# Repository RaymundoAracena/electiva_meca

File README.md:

# electiva_meca
aqui subire todas las tareas de electiva mecatronica

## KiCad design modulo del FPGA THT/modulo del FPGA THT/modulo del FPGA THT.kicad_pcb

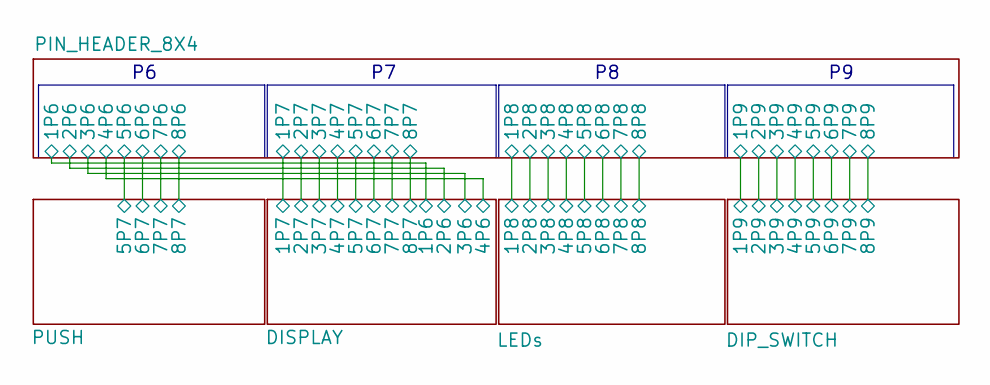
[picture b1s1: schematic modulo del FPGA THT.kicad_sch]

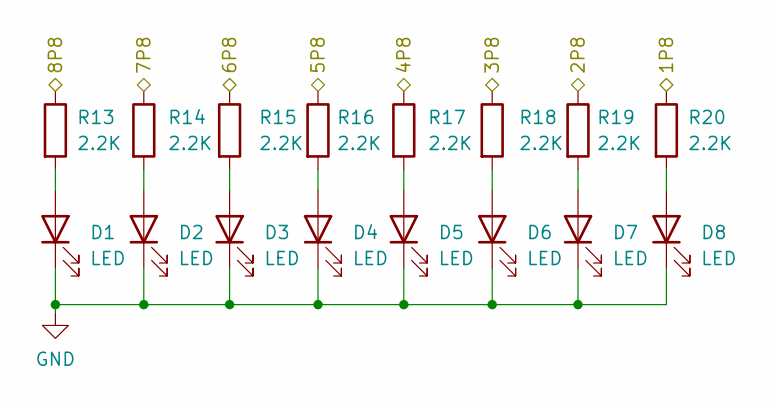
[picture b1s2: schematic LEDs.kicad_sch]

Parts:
D1, D2, D3, D4, D5, D6, D7, D8: LED; LED_0805_2012Metric
R13, R14, R15, R16, R17, R18, R19, R20: 2.2K; R_0805_2012Metric

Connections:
/LEDs/1P8: R20.1; also elsewhere on the board
/LEDs/2P8: R19.1; also elsewhere on the board
/LEDs/3P8: R18.1; also elsewhere on the board
/LEDs/4P8: R17.1; also elsewhere on the board
/LEDs/5P8: R16.1; also elsewhere on the board
/LEDs/6P8: R15.1; also elsewhere on the board
/LEDs/7P8: R14.1; also elsewhere on the board
/LEDs/8P8: R13.1; also elsewhere on the board
GND: D1.1 (K), D2.1 (K), D3.1 (K), D4.1 (K), D5.1 (K), D6.1 (K), D7.1 (K), D8.1 (K); also elsewhere on the board
unnamed: D1.2 (A), R13.2
unnamed: D2.2 (A), R14.2
unnamed: D3.2 (A), R15.2
unnamed: D4.2 (A), R16.2
unnamed: D5.2 (A), R17.2
unnamed: D6.2 (A), R18.2
unnamed: D7.2 (A), R19.2
unnamed: D8.2 (A), R20.2

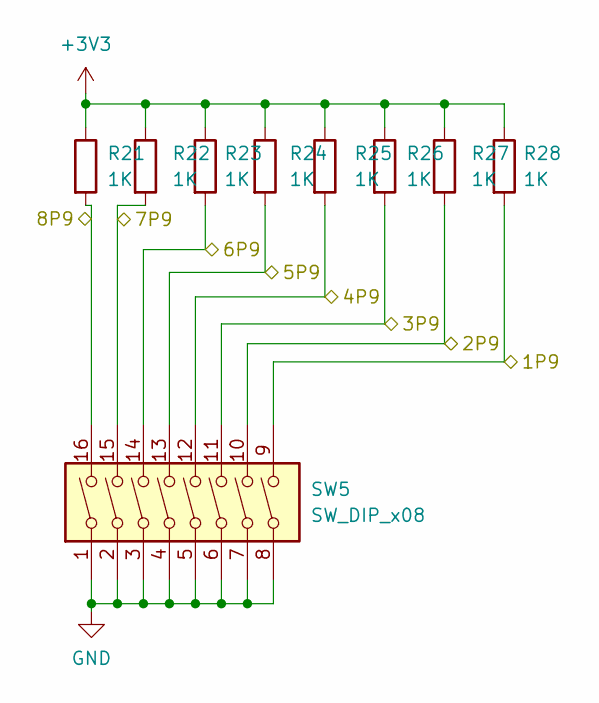
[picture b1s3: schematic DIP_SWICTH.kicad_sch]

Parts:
R21, R22, R23, R24, R25, R26, R27, R28: 1K; R_0805_2012Metric
SW5: SW_DIP_x08; SW_DIP_SPSTx08_Slide_6.7x21.88mm_W7.62mm_P2.54mm_LowProfile

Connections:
+3V3: R21.1, R22.1, R23.1, R24.1, R25.1, R26.1, R27.1, R28.1; also elsewhere on the board
/DIP_SWITCH/1P9: R28.2, SW5.9; also elsewhere on the board
/DIP_SWITCH/2P9: R27.2, SW5.10; also elsewhere on the board
/DIP_SWITCH/3P9: R26.2, SW5.11; also elsewhere on the board
/DIP_SWITCH/4P9: R25.2, SW5.12; also elsewhere on the board
/DIP_SWITCH/5P9: R24.2, SW5.13; also elsewhere on the board
/DIP_SWITCH/6P9: R23.2, SW5.14; also elsewhere on the board
/DIP_SWITCH/7P9: R22.2, SW5.15; also elsewhere on the board
/DIP_SWITCH/8P9: R21.2, SW5.16; also elsewhere on the board
GND: SW5.1, SW5.2, SW5.3, SW5.4, SW5.5, SW5.6, SW5.7, SW5.8; also elsewhere on the board

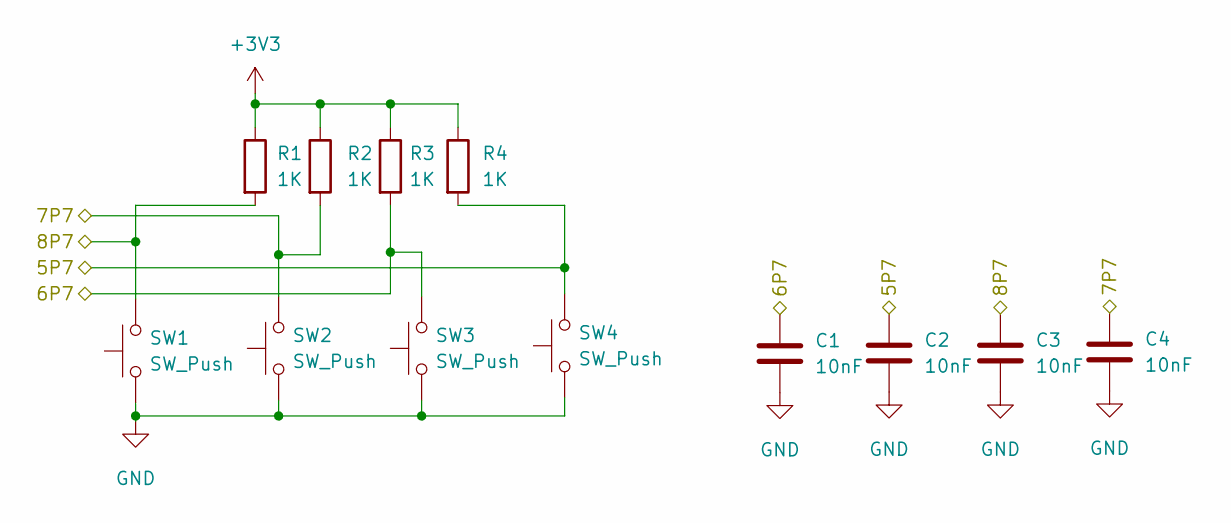
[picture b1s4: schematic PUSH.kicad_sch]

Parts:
C1, C2, C3, C4: 10nF; C_0805_2012Metric
R1, R2, R3, R4: 1K; R_0805_2012Metric
SW1, SW2, SW3, SW4: SW_Push; SW_PUSH_6mm

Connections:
+3V3: R1.1, R2.1, R3.1, R4.1; also elsewhere on the board
/PIN_HEADER_8X4/5P6: C2.1, R4.2, SW4.2; also elsewhere on the board
/PIN_HEADER_8X4/6P6: C1.1, R3.2, SW3.2; also elsewhere on the board
/PIN_HEADER_8X4/7P6: C4.1, R2.2, SW2.2; also elsewhere on the board
/PIN_HEADER_8X4/8P6: C3.1, R1.2, SW1.2; also elsewhere on the board
GND: C1.2, C2.2, C3.2, C4.2, SW1.1, SW2.1, SW3.1, SW4.1; also elsewhere on the board

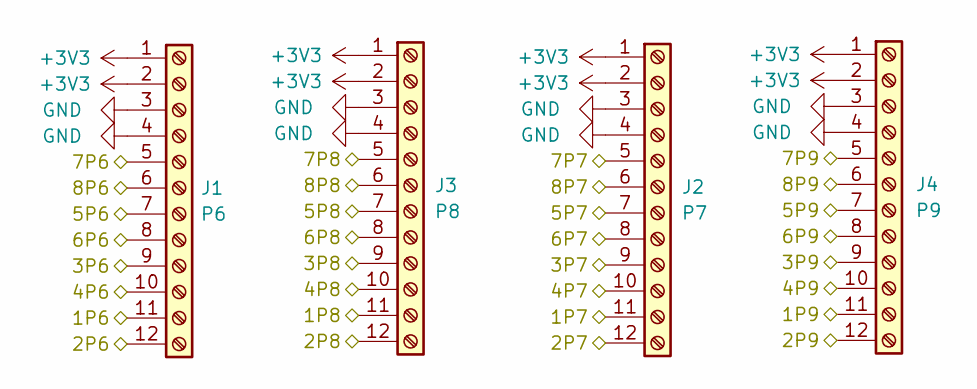
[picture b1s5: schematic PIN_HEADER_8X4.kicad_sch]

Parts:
J1: P6; PinHeader_2x06_P2.54mm_Horizontal
J2: P7; PinHeader_2x06_P2.54mm_Horizontal
J3: P8; PinHeader_2x06_P2.54mm_Horizontal
J4: P9; PinHeader_2x06_P2.54mm_Horizontal

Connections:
+3V3: J1.1, J1.2, J2.1, J2.2, J3.1, J3.2, J4.1, J4.2; also elsewhere on the board
/DIP_SWITCH/1P9: J4.11; also elsewhere on the board
/DIP_SWITCH/2P9: J4.12; also elsewhere on the board
/DIP_SWITCH/3P9: J4.9; also elsewhere on the board
/DIP_SWITCH/4P9: J4.10; also elsewhere on the board
/DIP_SWITCH/5P9: J4.7; also elsewhere on the board
/DIP_SWITCH/6P9: J4.8; also elsewhere on the board
/DIP_SWITCH/7P9: J4.5; also elsewhere on the board
/DIP_SWITCH/8P9: J4.6; also elsewhere on the board
/DISPLAY/1P6: J1.11; also elsewhere on the board
/DISPLAY/1P7: J2.11; also elsewhere on the board
/DISPLAY/2P6: J1.12; also elsewhere on the board
/DISPLAY/2P7: J2.12; also elsewhere on the board
/DISPLAY/3P6: J1.9; also elsewhere on the board
/DISPLAY/3P7: J2.9; also elsewhere on the board
/DISPLAY/4P6: J1.10; also elsewhere on the board
/DISPLAY/4P7: J2.10; also elsewhere on the board
/DISPLAY/5P7: J2.7; also elsewhere on the board
/DISPLAY/6P7: J2.8; also elsewhere on the board
/DISPLAY/7P7: J2.5; also elsewhere on the board
/DISPLAY/8P7: J2.6; also elsewhere on the board
/LEDs/1P8: J3.11; also elsewhere on the board
/LEDs/2P8: J3.12; also elsewhere on the board
/LEDs/3P8: J3.9; also elsewhere on the board
/LEDs/4P8: J3.10; also elsewhere on the board
/LEDs/5P8: J3.7; also elsewhere on the board
/LEDs/6P8: J3.8; also elsewhere on the board
/LEDs/7P8: J3.5; also elsewhere on the board
/LEDs/8P8: J3.6; also elsewhere on the board
/PIN_HEADER_8X4/5P6: J1.7; also elsewhere on the board
/PIN_HEADER_8X4/6P6: J1.8; also elsewhere on the board
/PIN_HEADER_8X4/7P6: J1.5; also elsewhere on the board
/PIN_HEADER_8X4/8P6: J1.6; also elsewhere on the board
GND: J1.3, J1.4, J2.3, J2.4, J3.3, J3.4, J4.3, J4.4; also elsewhere on the board

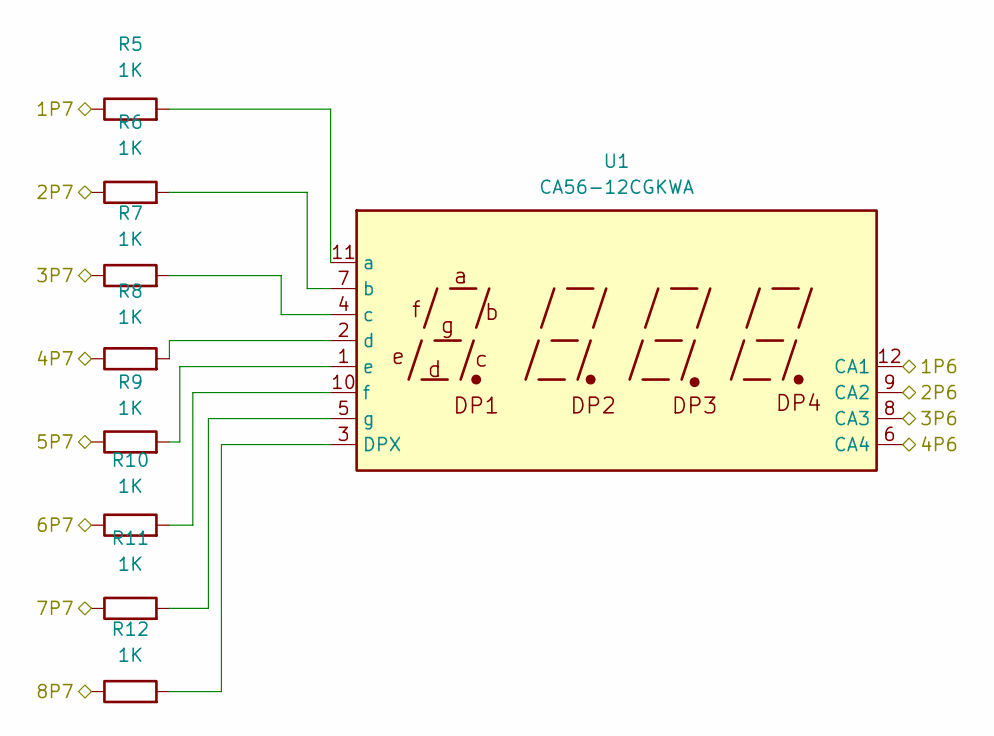
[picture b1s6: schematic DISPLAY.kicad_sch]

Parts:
R5, R6, R7, R8, R9, R10, R11, R12: 1K; R_0805_2012Metric
U1: CA56-12CGKWA

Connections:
/DISPLAY/1P6: U1.12 (CA1); also elsewhere on the board
/DISPLAY/1P7: R5.1; also elsewhere on the board
/DISPLAY/2P6: U1.9 (CA2); also elsewhere on the board
/DISPLAY/2P7: R6.1; also elsewhere on the board
/DISPLAY/3P6: U1.8 (CA3); also elsewhere on the board
/DISPLAY/3P7: R7.1; also elsewhere on the board
/DISPLAY/4P6: U1.6 (CA4); also elsewhere on the board
/DISPLAY/4P7: R8.1; also elsewhere on the board
/DISPLAY/5P7: R9.1; also elsewhere on the board
/DISPLAY/6P7: R10.1; also elsewhere on the board
/DISPLAY/7P7: R11.1; also elsewhere on the board
/DISPLAY/8P7: R12.1; also elsewhere on the board
unnamed: R12.2, U1.3 (DPX)
unnamed: R5.2, U1.11 (a)
unnamed: R6.2, U1.7 (b)
unnamed: R7.2, U1.4 (c)
unnamed: R8.2, U1.2 (d)
unnamed: R9.2, U1.1 (e)
unnamed: R10.2, U1.10 (f)
unnamed: R11.2, U1.5 (g)

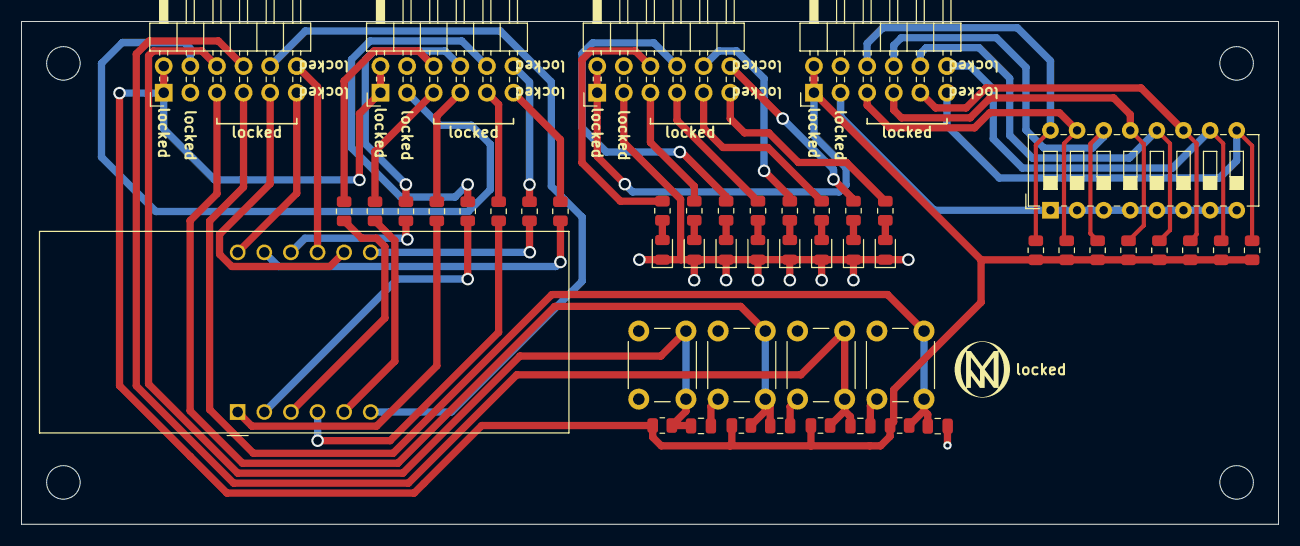
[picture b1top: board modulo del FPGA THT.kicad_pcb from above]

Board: 2 copper layers, 120.0 x 48.0 mm, 50 parts (0 on the bottom side), 50 nets.

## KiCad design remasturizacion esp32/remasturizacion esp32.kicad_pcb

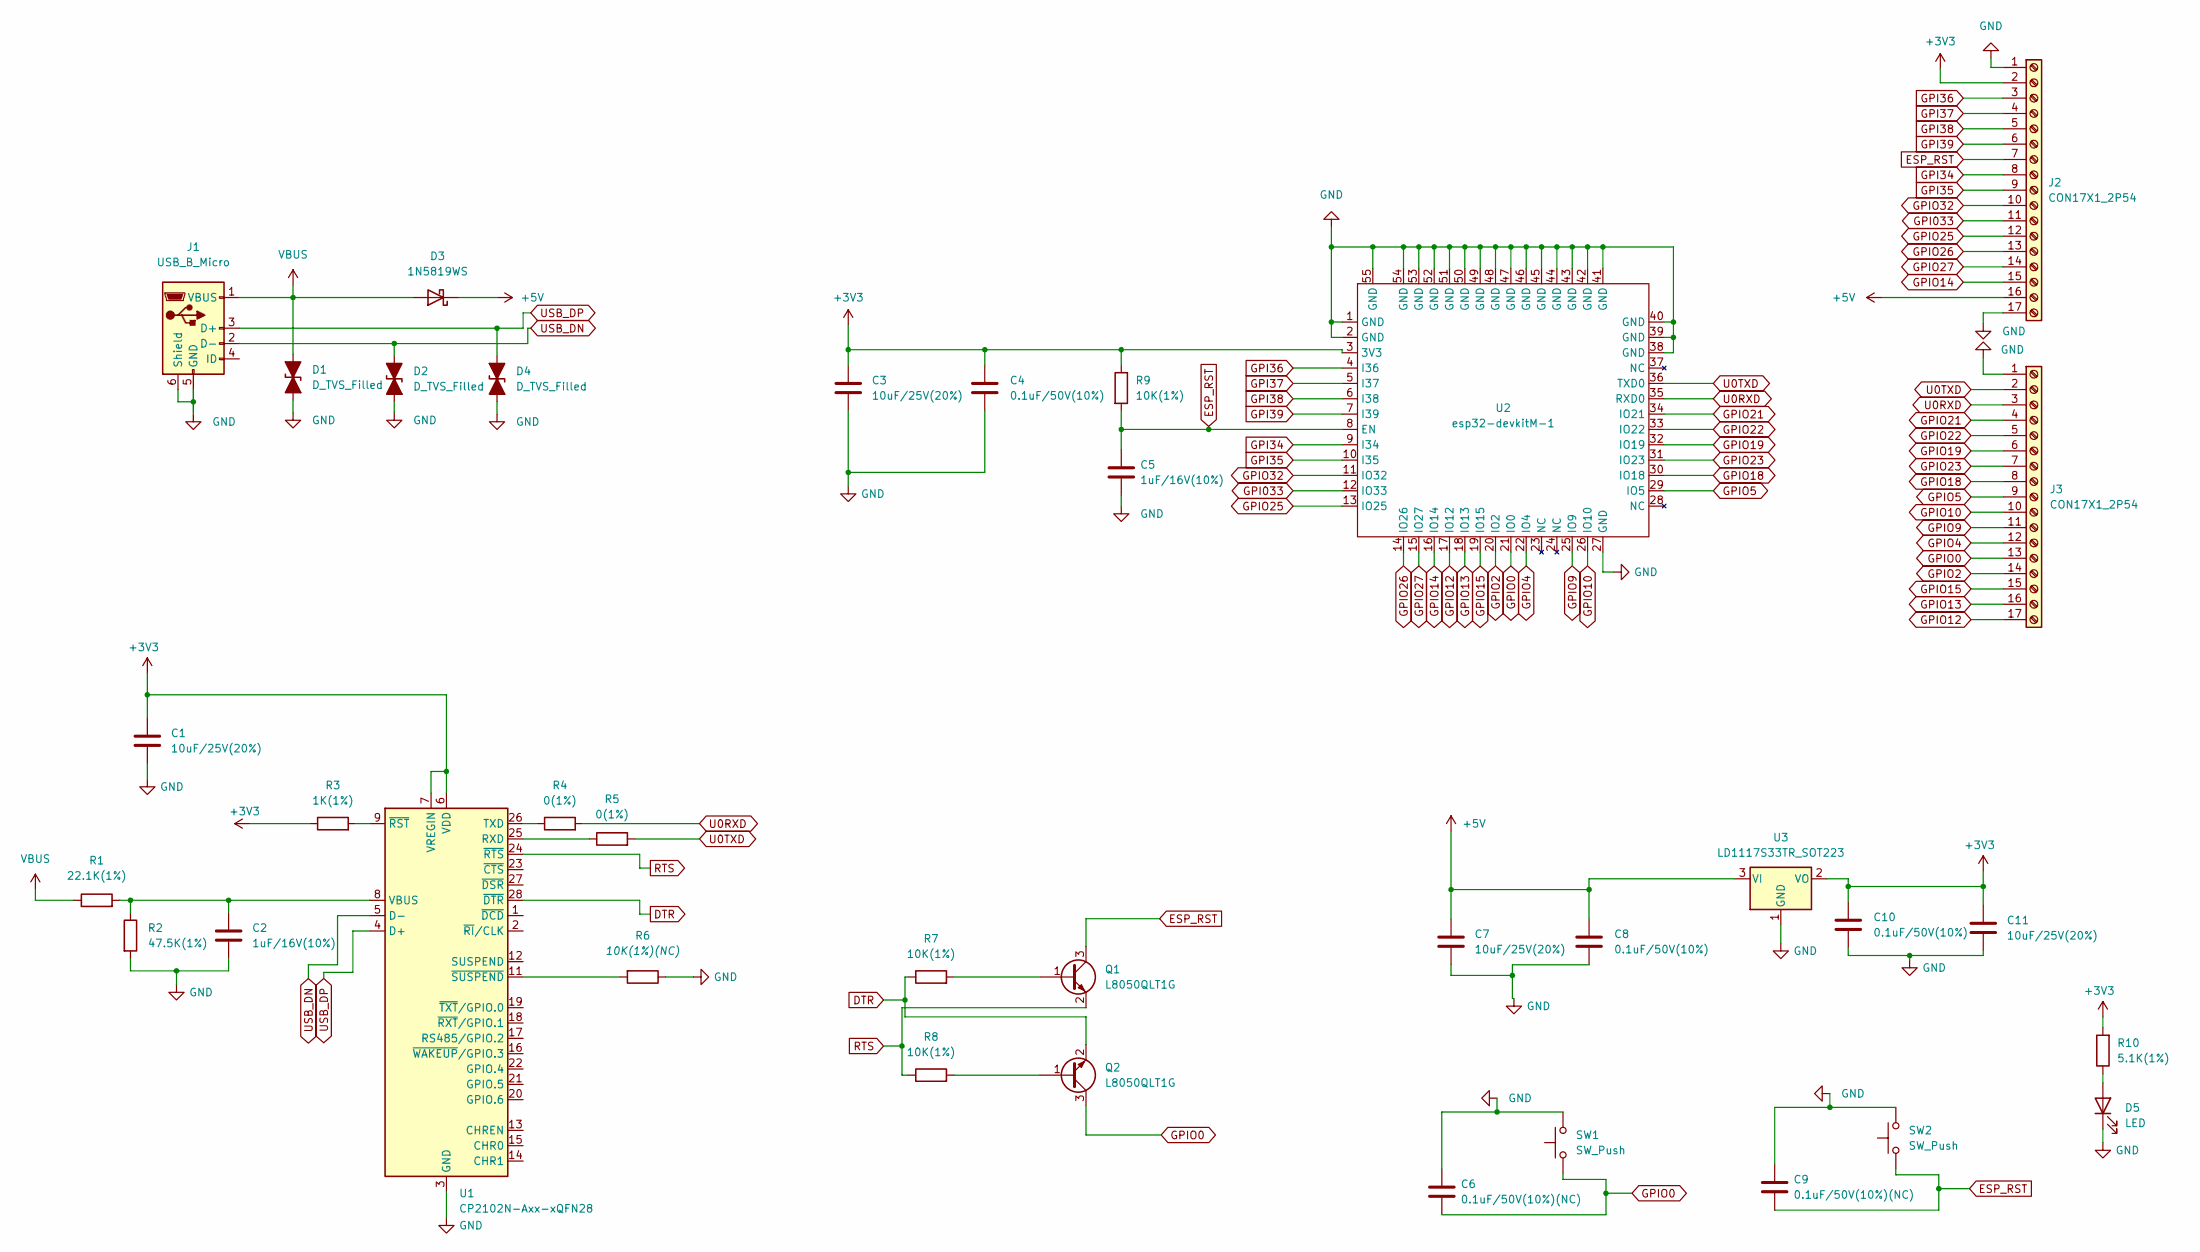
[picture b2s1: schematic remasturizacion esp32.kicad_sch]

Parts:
C1, C3, C7, C11: 10uF/25V(20%); C_0805_2012Metric
C2, C5: 1uF/16V(10%); C_0805_2012Metric
C4, C8, C10: 0.1uF/50V(10%); C_0805_2012Metric
C6, C9: 0.1uF/50V(10%)(NC); C_0805_2012Metric
D1, D2, D4: D_TVS_Filled; TVS_LESD5D5.0CT1G
D3: 1N5819WS; D_SOD-323
D5: LED; LED_0805_2012Metric
J1: USB_B_Micro; USB_Micro-B_Wuerth_629105150521
J2, J3: CON17X1_2P54; PinHeader_1x17_P2.54mm_Vertical
Q1, Q2: L8050QLT1G; SOT-23
R1: 22.1K(1%); R_0805_2012Metric
R2: 47.5K(1%); R_0805_2012Metric
R3: 1K(1%); R_0805_2012Metric
R4, R5: 0(1%); R_0805_2012Metric
R6: 10K(1%)(NC); R_0805_2012Metric
R7, R8, R9: 10K(1%); R_0805_2012Metric
R10: 5.1K(1%); R_0805_2012Metric
SW1, SW2: SW_Push; SW_SPST_PTS810
U1: CP2102N-Axx-xQFN28; QFN-28-1EP_5x5mm_P0.5mm_EP3.35x3.35mm
U2: esp32-devkitM-1
U3: LD1117S33TR_SOT223; SOT-223-3_TabPin2

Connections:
+3V3: C1.1, C3.1, C4.1, C10.1, C11.1, J2.2, R3.1, R9.1, R10.2, U1.6 (VDD), U1.7 (VREGIN), U2.3 (3V3), U3.2 (VO)
+5V: C7.1, C8.1, D3.1 (K), J2.16, U3.3 (VI)
DTR: Q2.2 (E), R7.1, U1.28 (~DTR)
ESP_RST: C5.1, C9.2, J2.7, Q1.3 (C), R9.2, SW2.1, U2.8 (EN)
GND: C1.2, C2.2, C3.2, C4.2, C5.2, C6.1, C7.2, C8.2, C9.1, C10.2, C11.2, D1.1 (A1), D2.1 (A1), D4.1 (A1), D5.1 (K), J1.5 (GND), J1.6 (Shield), J2.1, J2.17, J3.1, R2.2, R6.1, SW1.2, SW2.2, U1.3 (GND), U1.29 (GND), U2.1 (GND), U2.2 (GND), U2.27 (GND), U2.38 (GND), U2.39 (GND), U2.40 (GND), U2.41 (GND), U2.42 (GND), U2.43 (GND), U2.44 (GND), U2.45 (GND), U2.46 (GND), U2.47 (GND), U2.48 (GND), U2.49 (GND), U2.50 (GND), U2.51 (GND), U2.52 (GND), U2.53 (GND), U2.54 (GND), U2.55 (GND), U3.1 (GND)
GPI033: J2.11, U2.12 (IO33)
GPI34: J2.8, U2.9 (I34)
GPI35: J2.9, U2.10 (I35)
GPI36: J2.3, U2.4 (I36)
GPI37: J2.4, U2.5 (I37)
GPI38: J2.5, U2.6 (I38)
GPI39: J2.6, U2.7 (I39)
GPIO0: C6.2, J3.13, Q2.3 (C), SW1.1, U2.21 (IO0)
GPIO2: J3.14, U2.20 (IO2)
GPIO4: J3.12, U2.22 (IO4)
GPIO5: J3.9, U2.29 (IO5)
GPIO9: J3.11, U2.25 (IO9)
GPIO10: J3.10, U2.26 (IO10)
GPIO12: J3.17, U2.17 (IO12)
GPIO13: J3.16, U2.18 (IO13)
GPIO14: J2.15, U2.16 (IO14)
GPIO15: J3.15, U2.19 (IO15)
GPIO18: J3.8, U2.30 (IO18)
GPIO19: J3.6, U2.32 (IO19)
GPIO21: J3.4, U2.34 (IO21)
GPIO22: J3.5, U2.33 (IO22)
GPIO23: J3.7, U2.31 (IO23)
GPIO25: J2.12, U2.13 (IO25)
GPIO26: J2.13, U2.14 (IO26)
GPIO27: J2.14, U2.15 (IO27)
GPIO32: J2.10, U2.11 (IO32)
unnamed: C2.1, R1.2, R2.1, U1.8 (VBUS)
unnamed: D5.2 (A), R10.1
unnamed: Q1.1 (B), R7.2
unnamed: Q2.1 (B), R8.2
unnamed: R3.2, U1.9 (~RST)
unnamed: R4.1, U1.26 (TXD)
unnamed: R5.1, U1.25 (RXD)
unnamed: R6.2, U1.11 (~SUSPEND)
RTS: Q1.2 (E), R8.1, U1.24 (~RTS)
U0RXD: J3.3, R4.2, U2.35 (RXD0)
U0TXD: J3.2, R5.2, U2.36 (TXD0)
USB_DN: D2.2 (A2), J1.2 (D-), U1.5 (D-)
USB_DP: D4.2 (A2), J1.3 (D+), U1.4 (D+)
VBUS: D1.2 (A2), D3.2 (A), J1.1 (VBUS), R1.1

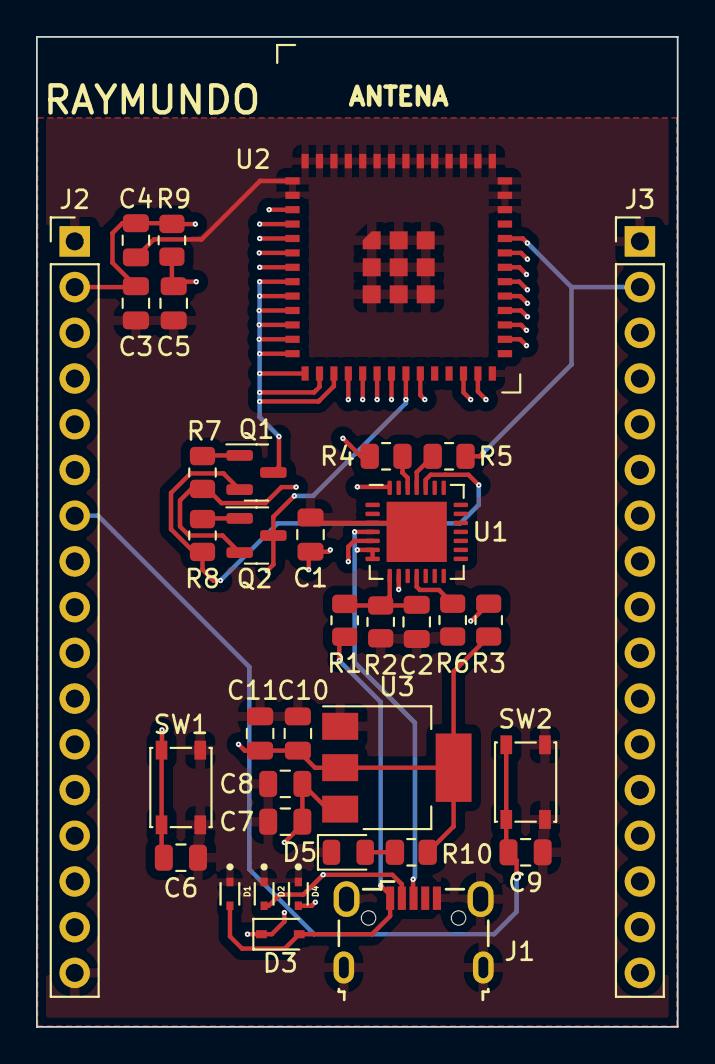
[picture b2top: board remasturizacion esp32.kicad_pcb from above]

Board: 4 copper layers, 35.6 x 55.0 mm, 36 parts (0 on the bottom side), 45 nets.

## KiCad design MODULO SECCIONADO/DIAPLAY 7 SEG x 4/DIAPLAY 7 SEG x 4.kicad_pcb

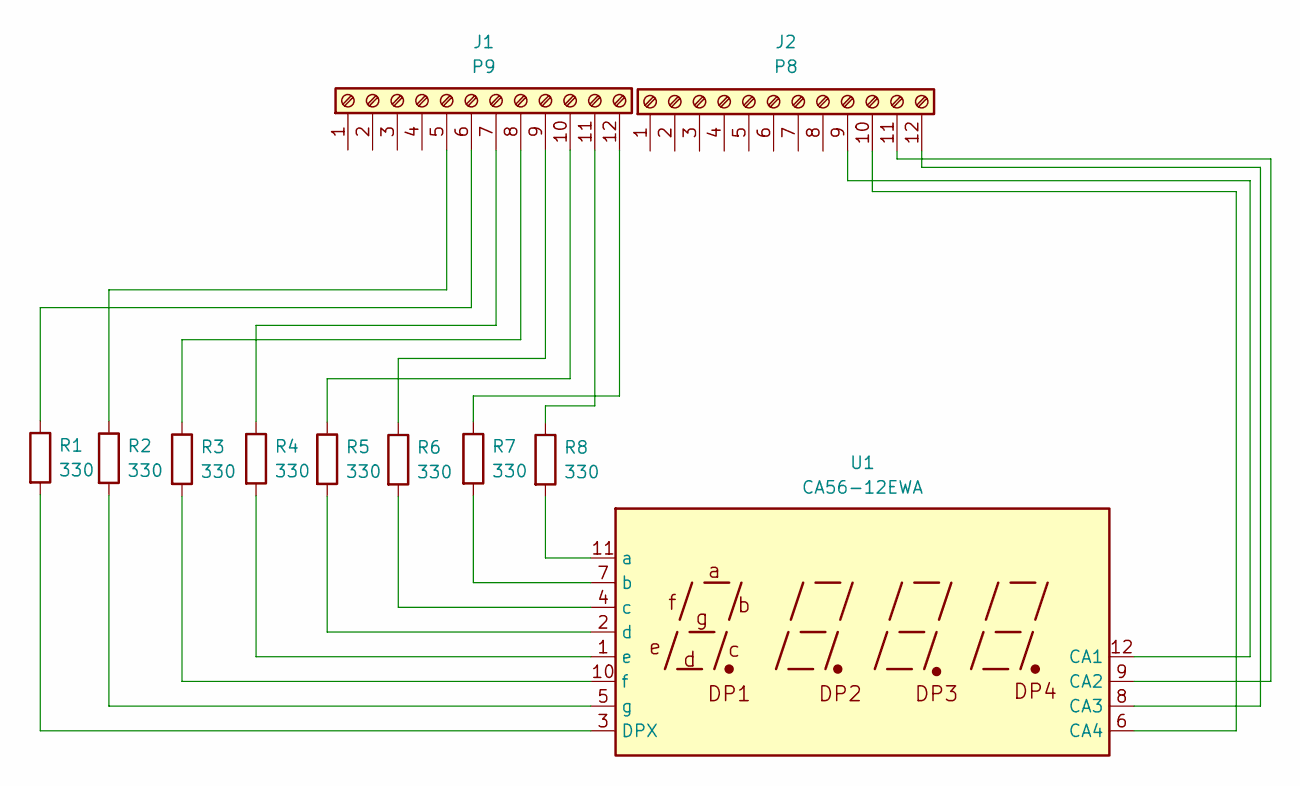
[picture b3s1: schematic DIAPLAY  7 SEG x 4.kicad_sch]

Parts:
J1: P9; PinHeader_2x06_P2.54mm_Horizontal
J2: P8; PinHeader_2x06_P2.54mm_Horizontal
R1, R2, R3, R4, R5, R6, R7, R8: 330; R_Axial_DIN0207_L6.3mm_D2.5mm_P7.62mm_Horizontal
U1: CA56-12EWA

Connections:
unnamed: J1.5, R2.1
unnamed: J1.6, R1.1
unnamed: J1.7, R4.1
unnamed: J1.8, R3.1
unnamed: J1.9, R6.1
unnamed: J1.10, R5.1
unnamed: J1.11, R8.1
unnamed: J1.12, R7.1
unnamed: J2.9, U1.12 (CA1)
unnamed: J2.10, U1.6 (CA4)
unnamed: J2.11, U1.9 (CA2)
unnamed: J2.12, U1.8 (CA3)
unnamed: R1.2, U1.3 (DPX)
unnamed: R2.2, U1.5 (g)
unnamed: R3.2, U1.10 (f)
unnamed: R4.2, U1.1 (e)
unnamed: R5.2, U1.2 (d)
unnamed: R6.2, U1.4 (c)
unnamed: R7.2, U1.7 (b)
unnamed: R8.2, U1.11 (a)

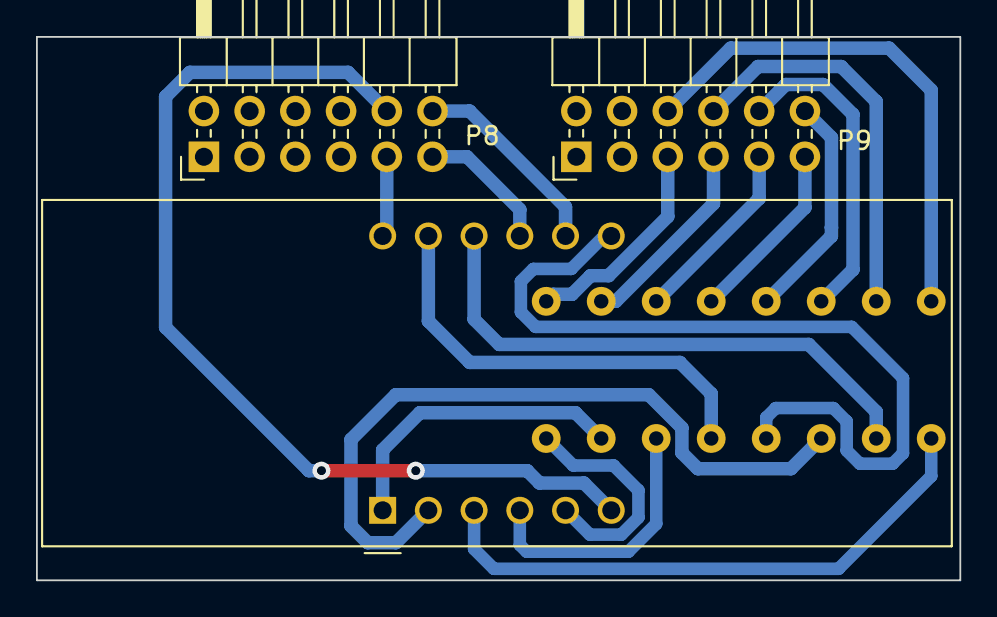
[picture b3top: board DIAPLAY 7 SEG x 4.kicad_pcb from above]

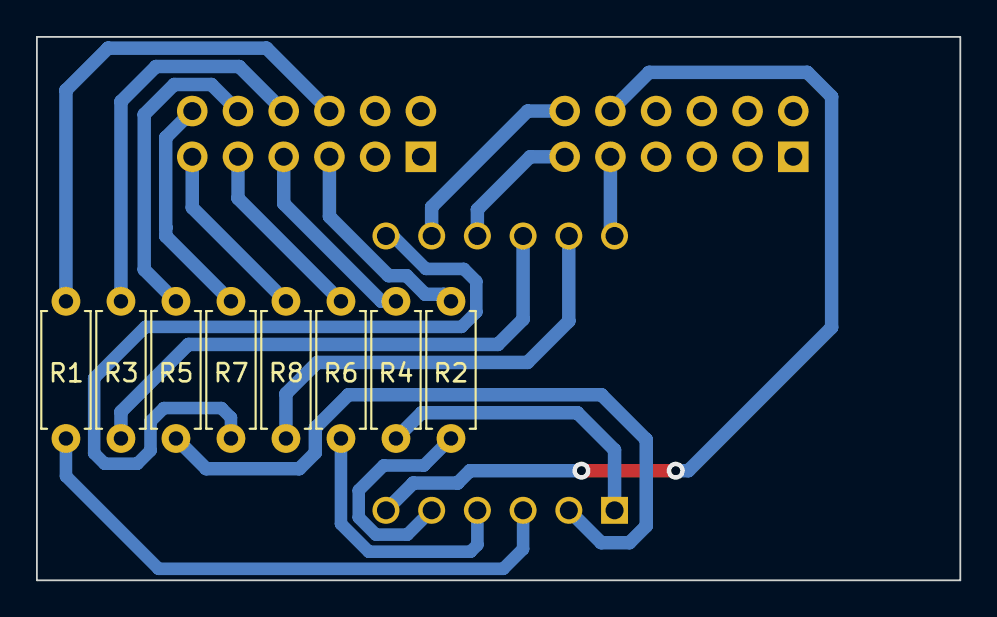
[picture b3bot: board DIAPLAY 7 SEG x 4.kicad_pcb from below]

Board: 2 copper layers, 51.3 x 30.2 mm, 11 parts (8 on the bottom side), 20 nets.

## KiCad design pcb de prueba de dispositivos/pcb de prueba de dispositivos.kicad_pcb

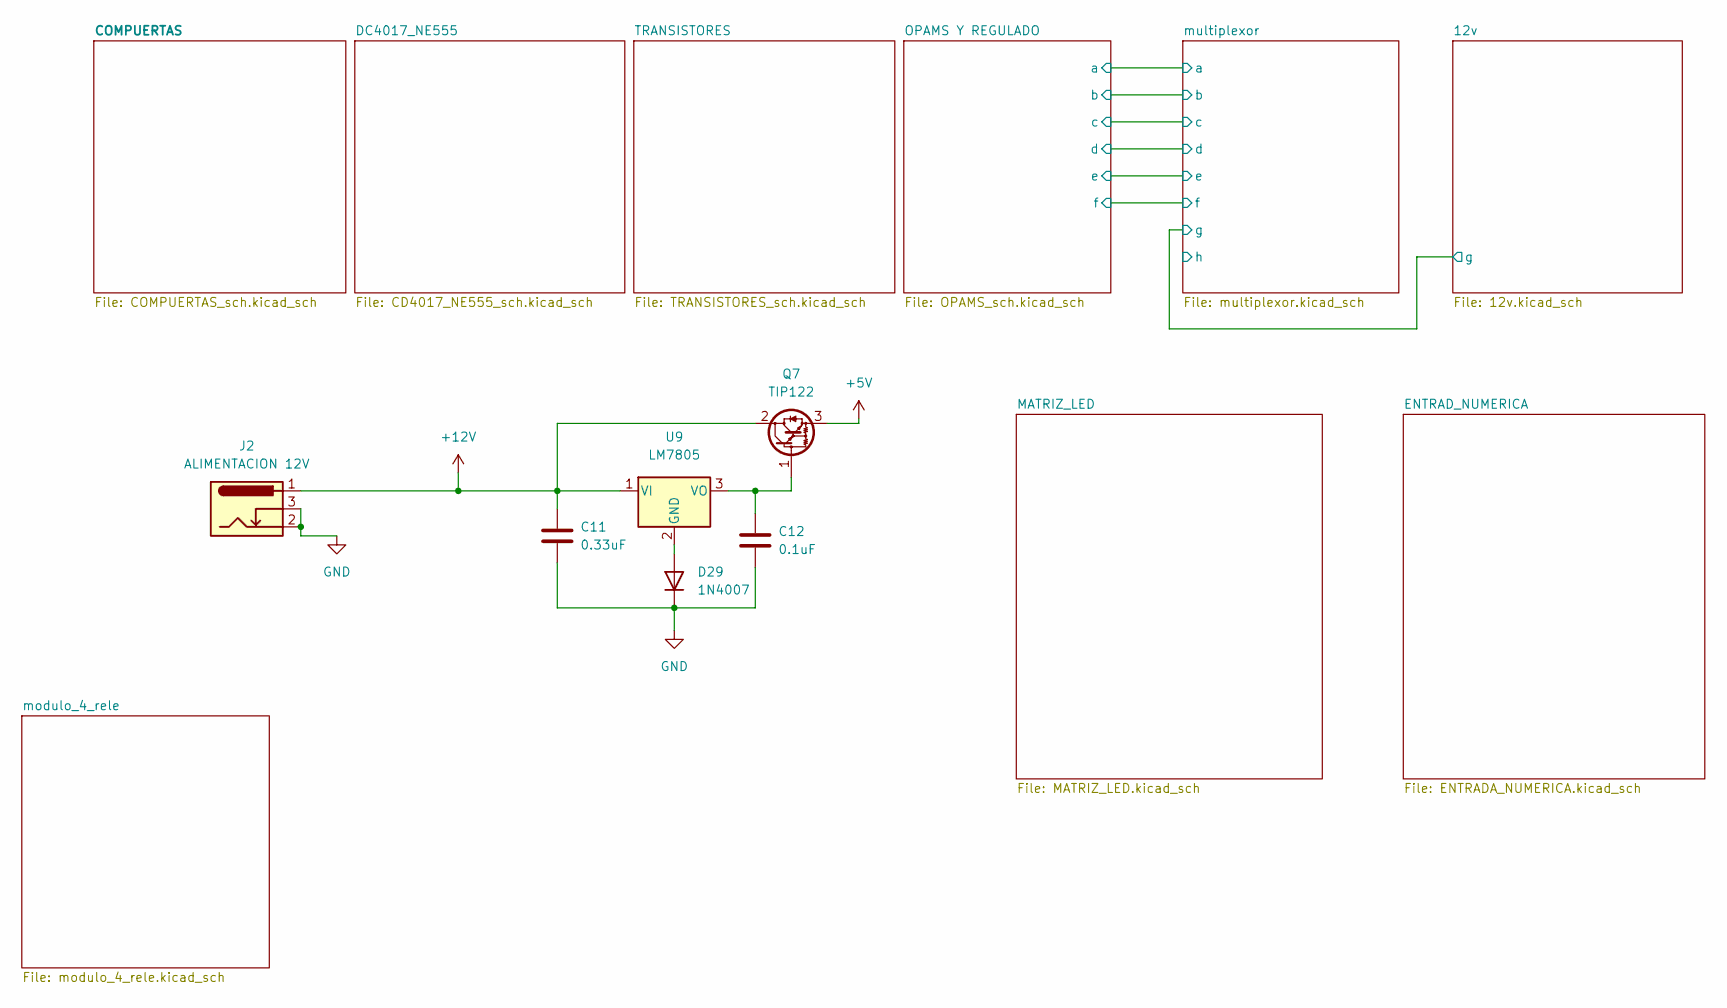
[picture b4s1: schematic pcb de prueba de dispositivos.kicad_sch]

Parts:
C11: 0.33uF; C_Disc_D5.0mm_W2.5mm_P5.00mm
C12: 0.1uF; C_Disc_D5.0mm_W2.5mm_P5.00mm
D29: 1N4007; D_DO-41_SOD81_P10.16mm_Horizontal
J2: ALIMENTACION 12V; BarrelJack_GCT_DCJ200-10-A_Horizontal
Q7: TIP122; TO-220-3_Vertical
U9: LM7805; TO-220-3_Vertical

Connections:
+5V: Q7.3 (E); also elsewhere on the board
+12V: C11.1, J2.1, Q7.2 (C), U9.1 (VI); also elsewhere on the board
GND: C11.2, C12.2, D29.1 (K), J2.2, J2.3; also elsewhere on the board
unnamed: C12.1, Q7.1 (B), U9.3 (VO)
unnamed: D29.2 (A), U9.2 (GND)

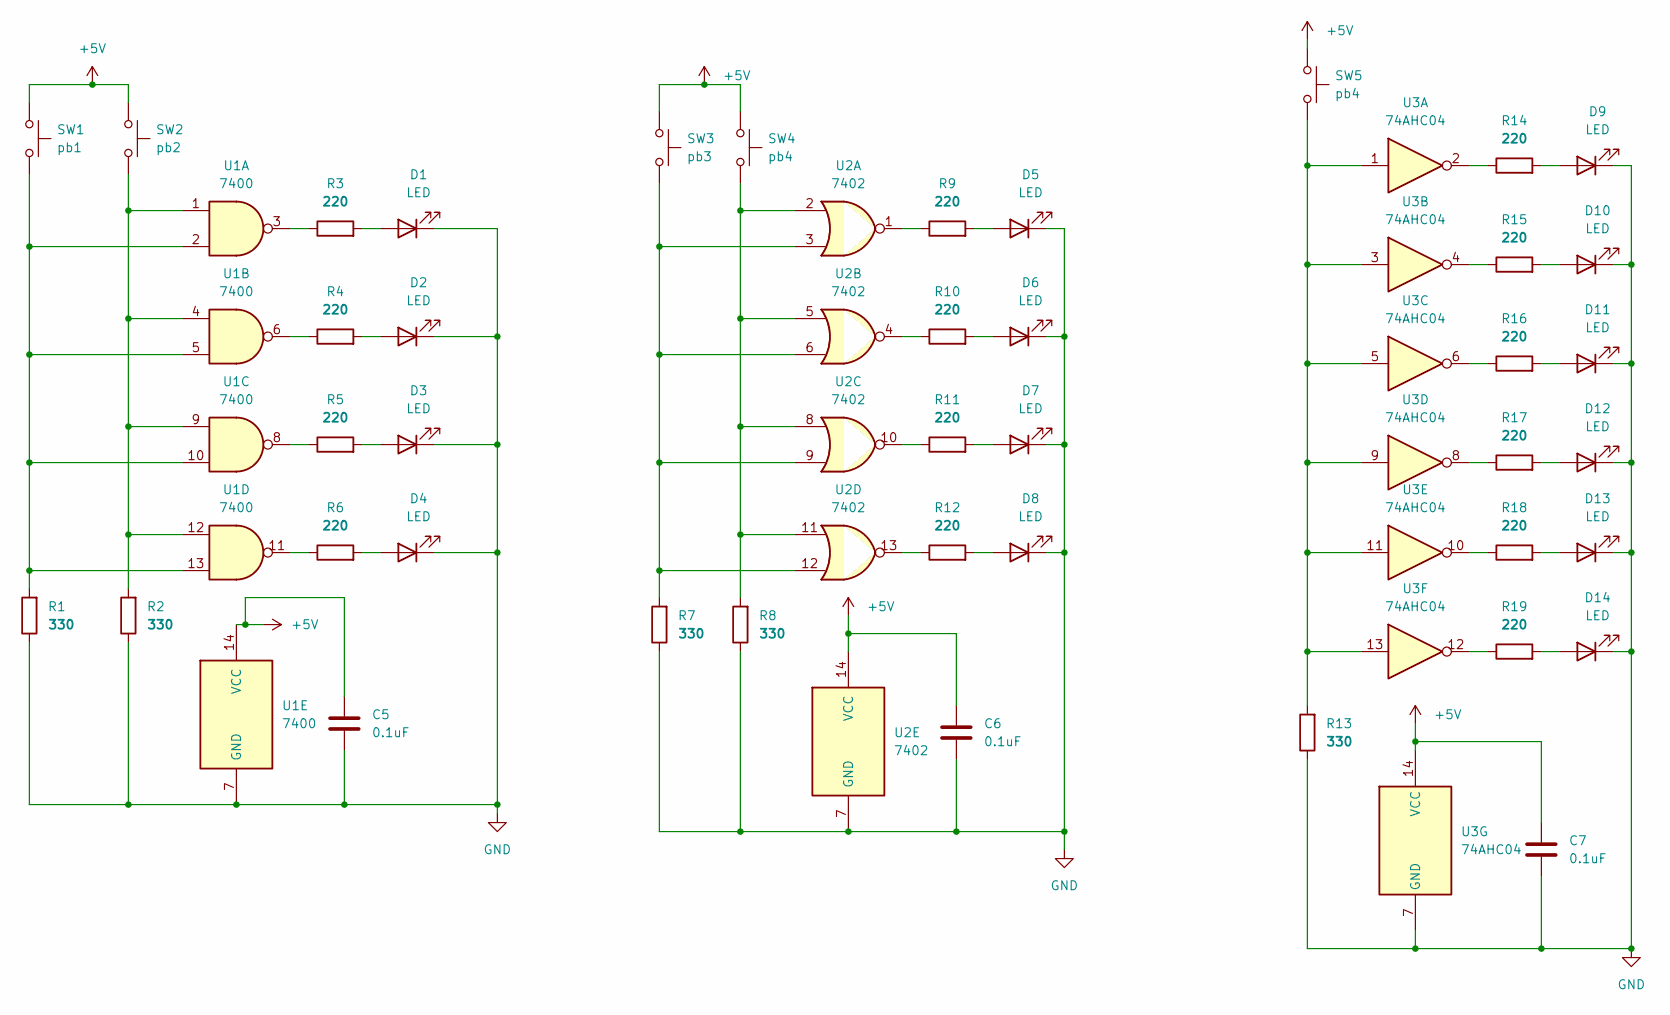
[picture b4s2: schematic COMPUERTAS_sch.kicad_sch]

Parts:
C5, C6, C7: 0.1uF; C_Disc_D5.0mm_W2.5mm_P5.00mm
D1, D2, D3, D4, D5, D6, D7, D8, D9, D10, D11, D12, D13, D14: LED; LED_D5.0mm
R1, R2, R7, R8, R13: 330; R_Axial_DIN0207_L6.3mm_D2.5mm_P10.16mm_Horizontal
R3, R4, R5, R6, R9, R10, R11, R12, R14, R15, R16, R17, R18, R19: 220; R_Axial_DIN0207_L6.3mm_D2.5mm_P10.16mm_Horizontal
SW1: pb1; SW_PUSH_6mm
SW2: pb2; SW_PUSH_6mm
SW3: pb3; SW_PUSH_6mm
SW4, SW5: pb4; SW_PUSH_6mm
U1: 7400; DIP-14_W7.62mm_LongPads
U2: 7402; DIP-14_W7.62mm_LongPads
U3: 74AHC04; DIP-14_W7.62mm_LongPads

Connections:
+5V: C5.2, C6.2, C7.2, SW1.1, SW2.1, SW3.1, SW4.1, SW5.1, U1.14 (VCC), U2.14 (VCC), U3.14 (VCC); also elsewhere on the board
GND: C5.1, C6.1, C7.1, D1.1 (K), D2.1 (K), D3.1 (K), D4.1 (K), D5.1 (K), D6.1 (K), D7.1 (K), D8.1 (K), D9.1 (K), D10.1 (K), D11.1 (K), D12.1 (K), D13.1 (K), D14.1 (K), R1.1, R2.1, R7.1, R8.1, R13.1, U1.7 (GND), U2.7 (GND), U3.7 (GND); also elsewhere on the board
unnamed: D1.2 (A), R3.2
unnamed: D2.2 (A), R4.2
unnamed: D3.2 (A), R5.2
unnamed: D4.2 (A), R6.2
unnamed: D5.2 (A), R9.2
unnamed: D6.2 (A), R10.2
unnamed: D7.2 (A), R11.2
unnamed: D8.2 (A), R12.2
unnamed: D9.2 (A), R14.2
unnamed: D10.2 (A), R15.2
unnamed: D11.2 (A), R16.2
unnamed: D12.2 (A), R17.2
unnamed: D13.2 (A), R18.2
unnamed: D14.2 (A), R19.2
unnamed: R1.2, SW1.2, U1.2, U1.5, U1.10, U1.13
unnamed: R2.2, SW2.2, U1.1, U1.4, U1.9, U1.12
unnamed: R3.1, U1.3
unnamed: R4.1, U1.6
unnamed: R5.1, U1.8
unnamed: R6.1, U1.11
unnamed: R7.2, SW3.2, U2.3, U2.6, U2.9, U2.12
unnamed: R8.2, SW4.2, U2.2, U2.5, U2.8, U2.11
unnamed: R9.1, U2.1
unnamed: R10.1, U2.4
unnamed: R11.1, U2.10
unnamed: R12.1, U2.13
unnamed: R13.2, SW5.2, U3.1, U3.3, U3.5, U3.9, U3.11, U3.13
unnamed: R14.1, U3.2
unnamed: R15.1, U3.4
unnamed: R16.1, U3.6
unnamed: R17.1, U3.8
unnamed: R18.1, U3.10
unnamed: R19.1, U3.12

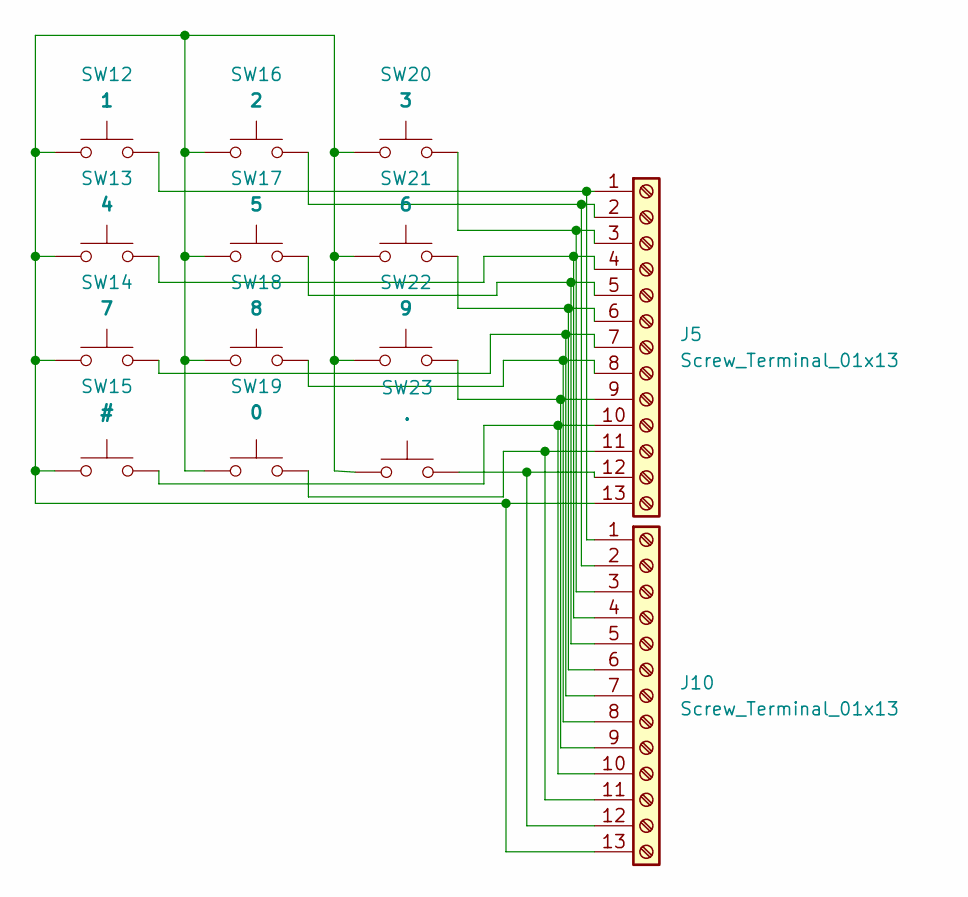
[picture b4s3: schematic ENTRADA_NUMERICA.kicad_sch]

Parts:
J5, J10: Screw_Terminal_01x13; PinSocket_1x13_P2.54mm_Vertical
SW12: 1; SW_PUSH_6mm
SW13: 4; SW_PUSH_6mm
SW14: 7; SW_PUSH_6mm
SW15: #; SW_PUSH_6mm
SW16: 2; SW_PUSH_6mm
SW17: 5; SW_PUSH_6mm
SW18: 8; SW_PUSH_6mm
SW19: 0; SW_PUSH_6mm
SW20: 3; SW_PUSH_6mm
SW21: 6; SW_PUSH_6mm
SW22: 9; SW_PUSH_6mm
SW23: .; SW_PUSH_6mm

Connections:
unnamed: J5.1, J10.1, SW12.2
unnamed: J5.2, J10.2, SW16.2
unnamed: J5.3, J10.3, SW20.2
unnamed: J5.4, J10.4, SW13.2
unnamed: J5.5, J10.5, SW17.2
unnamed: J5.6, J10.6, SW21.2
unnamed: J5.7, J10.7, SW14.2
unnamed: J5.8, J10.8, SW18.2
unnamed: J5.9, J10.9, SW22.2
unnamed: J5.10, J10.10, SW15.2
unnamed: J5.11, J10.11, SW19.2
unnamed: J5.12, J10.12, SW23.2
unnamed: J5.13, J10.13, SW12.1, SW13.1, SW14.1, SW15.1, SW16.1, SW17.1, SW18.1, SW19.1, SW20.1, SW21.1, SW22.1, SW23.1

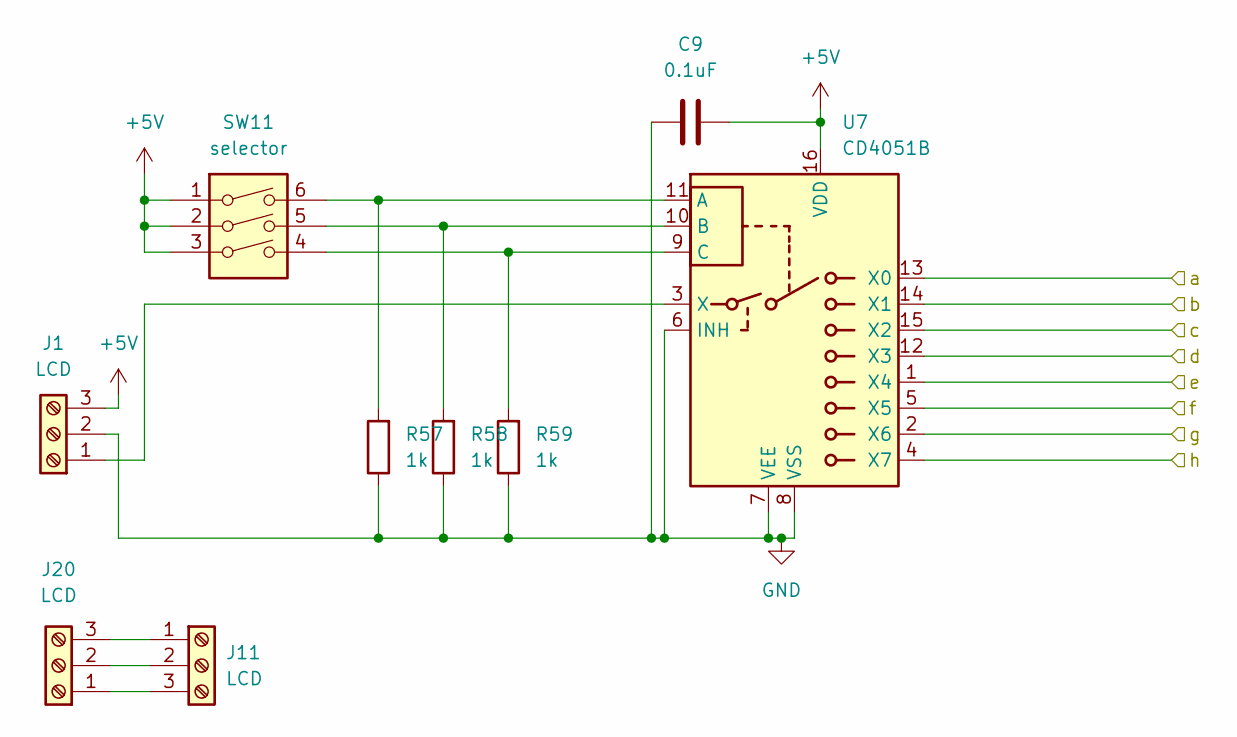
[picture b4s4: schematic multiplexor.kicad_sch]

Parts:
C9: 0.1uF; C_Disc_D5.0mm_W2.5mm_P5.00mm
J1, J20: LCD; JST_XH_B3B-XH-A_1x03_P2.50mm_Vertical
J11: LCD; PinHeader_1x03_P2.54mm_Vertical
R57, R58, R59: 1k; R_Axial_DIN0207_L6.3mm_D2.5mm_P10.16mm_Horizontal
SW11: selector; SW_DIP_SPSTx03_Slide_9.78x9.8mm_W7.62mm_P2.54mm
U7: CD4051B; DIP-16_W7.62mm_LongPads

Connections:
+5V: C9.1, J1.3, SW11.1, SW11.2, SW11.3, U7.16 (VDD); also elsewhere on the board
/12v/g: U7.2 (X6); also elsewhere on the board
/OPAMS Y REGULADO/a: U7.13 (X0); also elsewhere on the board
/OPAMS Y REGULADO/b: U7.14 (X1); also elsewhere on the board
/OPAMS Y REGULADO/c: U7.15 (X2); also elsewhere on the board
/OPAMS Y REGULADO/d: U7.12 (X3); also elsewhere on the board
/OPAMS Y REGULADO/e: U7.1 (X4); also elsewhere on the board
/OPAMS Y REGULADO/f: U7.5 (X5); also elsewhere on the board
/multiplexor/h: U7.4 (X7)
GND: C9.2, J1.2, R57.1, R58.1, R59.1, U7.6 (INH), U7.7 (VEE), U7.8 (VSS); also elsewhere on the board
unnamed: J1.1, U7.3 (X)
unnamed: J11.3, J20.1
unnamed: J11.2, J20.2
unnamed: J11.1, J20.3
unnamed: R57.2, SW11.6, U7.11 (A)
unnamed: R58.2, SW11.5, U7.10 (B)
unnamed: R59.2, SW11.4, U7.9 (C)
